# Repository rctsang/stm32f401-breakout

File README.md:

# STM32F401-Breakout

This is a breakout board for the STM32F401 using the [STM32F4Stamp](https://eleccelerator.com/stm32f4stamp-breakout-board/) (designed by Frank Zhao) as a reference.

It is untested, as this was only a personal project for gaining experience with PCB design.

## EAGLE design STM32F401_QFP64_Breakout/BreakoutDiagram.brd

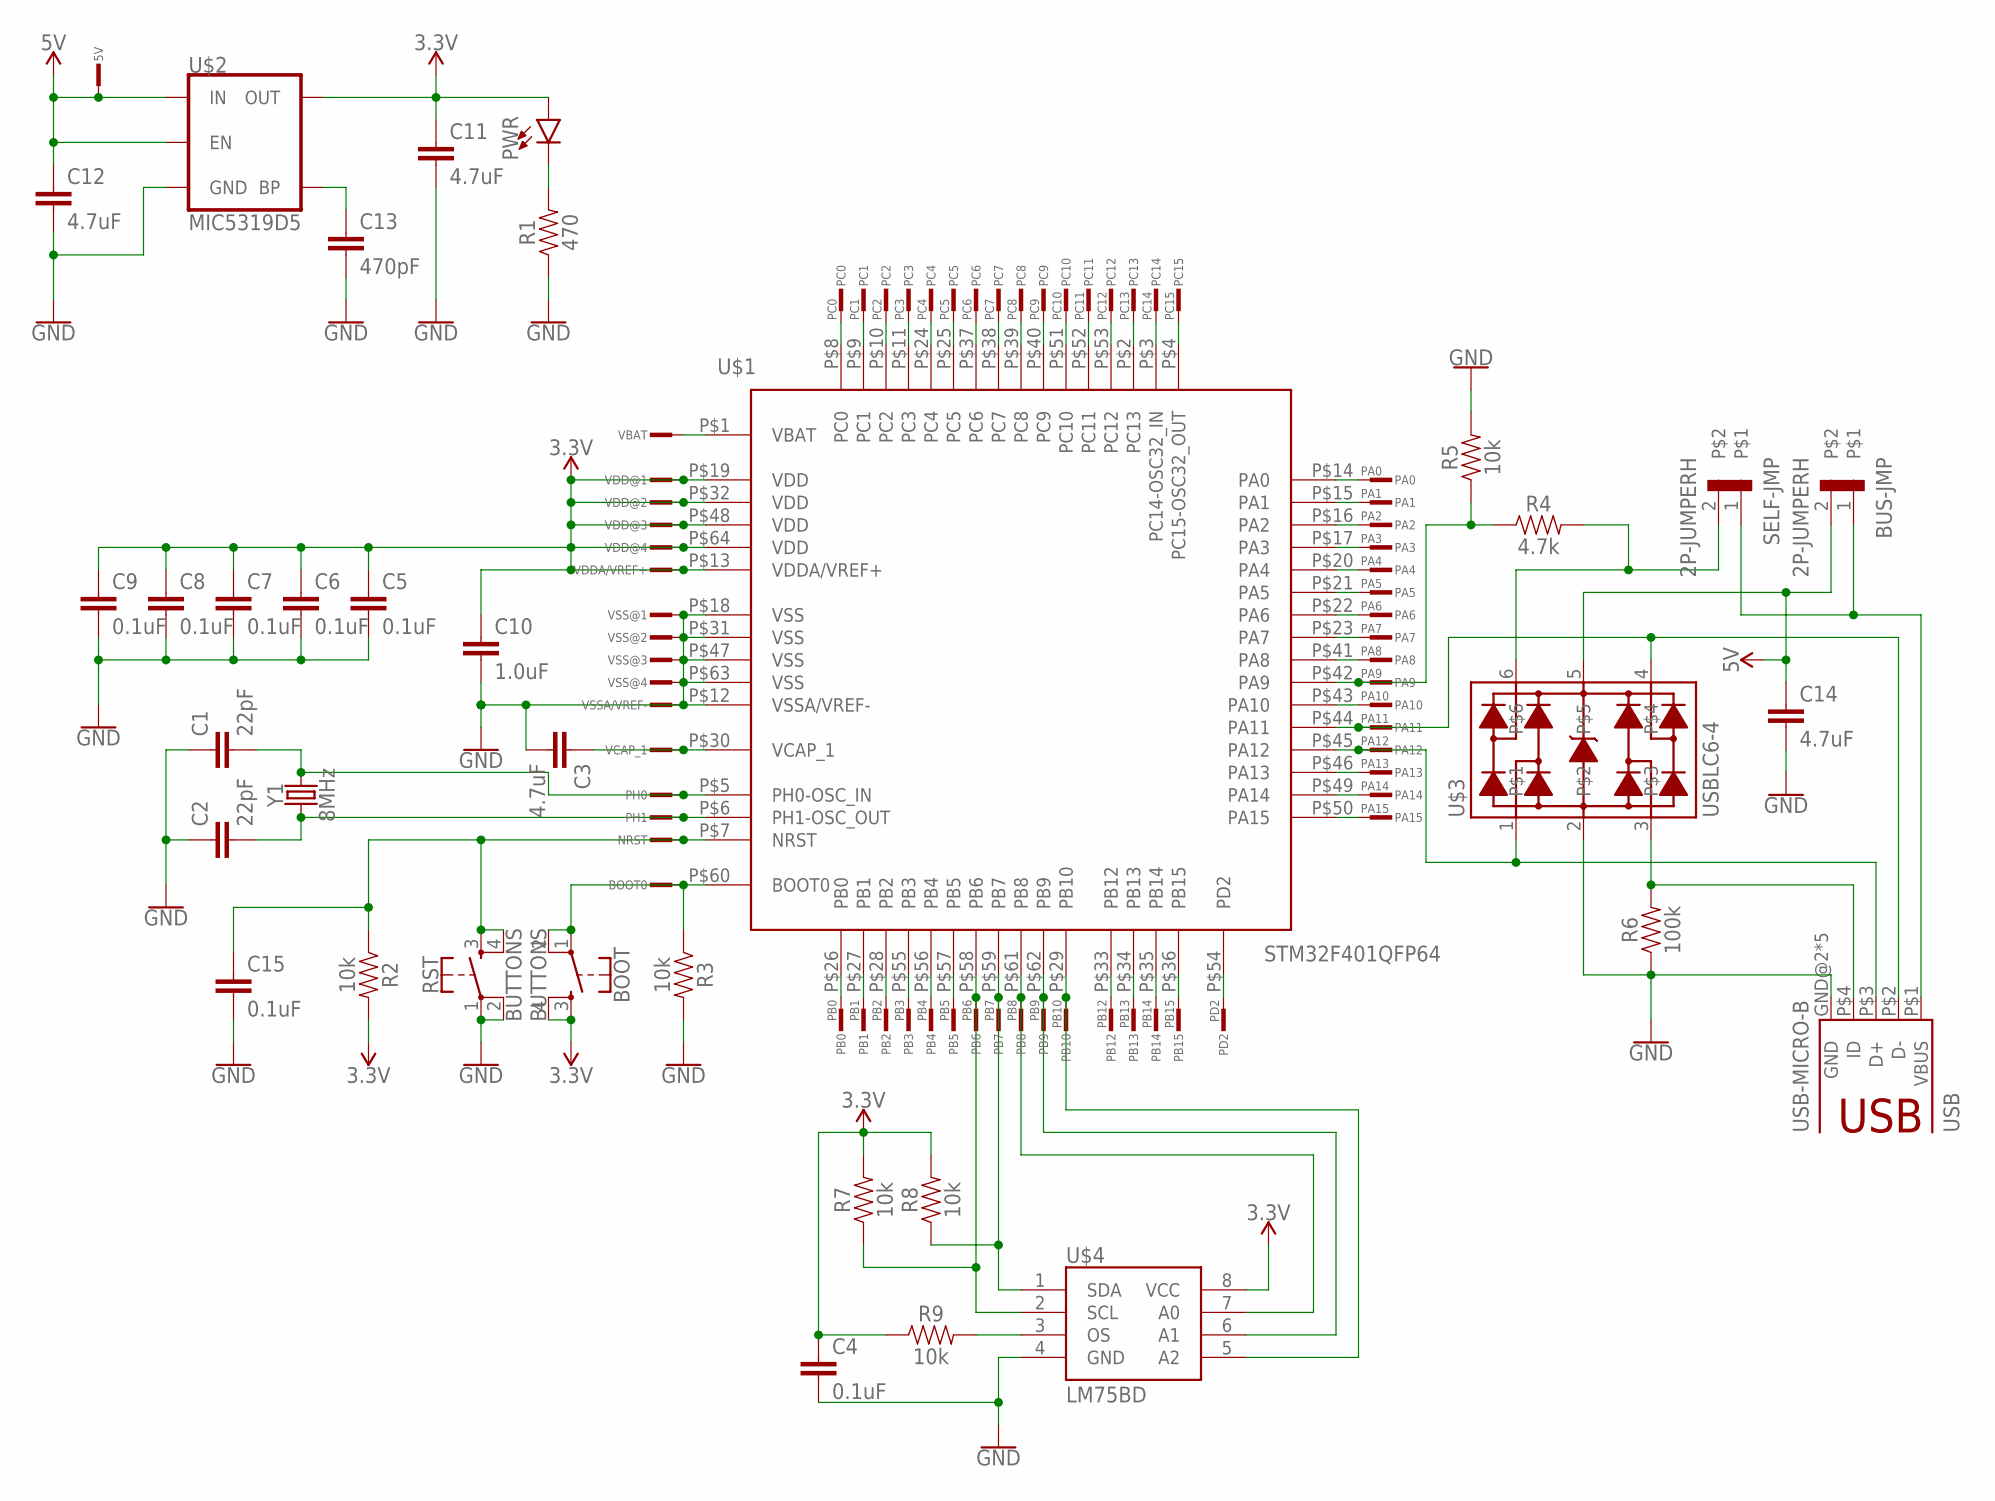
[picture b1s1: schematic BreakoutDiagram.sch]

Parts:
5V: PINV; 1X01
BOOT: BUTTONS; TACTILE_SWITCH_PTH_6.0MM
BOOT0: PINH; 1X01_HLABEL
BUS-JMP: 2P-JUMPERH; 1X02
C1, C2: 22pF; 0603
C3, C11, C12, C14: 4.7uF; 0603
C4, C15: 0.1uF; 0603
C5, C6, C7, C8, C9: 0.1uF; 0402
C10: 1.0uF; 0603
C13: 470pF; 0603
NRST: PINH; 1X01_HLABEL
PA0, PA1, PA2, PA3, PA4, PA5, PA6, PA7, PA8, PA9, PA10, PA11, PA12, PA13, PA14, PA15: PINH; 1X01_HLABEL
PB0, PB1, PB2, PB3, PB4, PB5, PB6, PB7, PB8, PB9, PB10, PB12, PB13, PB14, PB15: PINH; 1X01_HLABEL
PC0, PC1, PC2, PC3, PC4, PC5, PC6, PC7, PC8, PC9, PC10, PC11, PC12, PC13, PC14, PC15: PINH; 1X01_HLABEL
PD2: PINH; 1X01_HLABEL
PH0, PH1: PINH; 1X01_HLABEL
PWR: LED0603; LED-0603
R1: 470; 0402
R2, R3, R7, R8, R9: 10k; 0402
R4: 4.7k; 0603
R5: 10k; 0603
R6: 100k; 0603
RST: BUTTONS; TACTILE_SWITCH_PTH_6.0MM
SELF-JMP: 2P-JUMPERH; 1X02
U$1: STM32F401QFP64; LQFP64
U$2: MIC5319D5; SOT23-5
U$3: USBLC6-4; SOT23-6L
U$4: LM75BD; SO8
USB: USB-MICRO-B; USB-MICRO-B_SMD_CUT
VBAT: PINH; 1X01_HLABEL
VCAP_1: PINH; 1X01_HLABEL
VDD@1, VDD@2, VDD@3, VDD@4: PINH; 1X01_HLABEL
VDDA/VREF+: PINH; 1X01_HLABEL
VSS@1, VSS@2, VSS@3, VSS@4: PINH; 1X01_HLABEL
VSSA/VREF-: PINH; 1X01_HLABEL
Y1: 8MHz; CRYSTAL-SMD-5X3.2-2PAD

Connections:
3.3V: BOOT.3, BOOT.4, C4.1, C5.1, C6.1, C7.1, C8.1, C9.1, C10.1, C11.1, PWR.A, R2.2, R7.2, R8.2, R9.1, U$1.P$13 (VDDA/VREF+), U$1.P$19 (VDD), U$1.P$32 (VDD), U$1.P$48 (VDD), U$1.P$64 (VDD), U$2.5 (OUT), U$4.8 (VCC), VDD@1.1, VDD@2.1, VDD@3.1, VDD@4.1, VDDA/VREF+.1
5V: 5V.1, BUS-JMP.2, C12.1, C14.1, U$2.1 (IN), U$2.3 (EN), U$3.5
GND: C1.1, C2.1, C3.2, C4.2, C5.2, C6.2, C7.2, C8.2, C9.2, C10.2, C11.2, C12.2, C13.2, C14.2, C15.2, R1.1, R3.2, R5.2, R6.1, RST.1, RST.2, U$1.P$12 (VSSA/VREF-), U$1.P$18 (VSS), U$1.P$31 (VSS), U$1.P$47 (VSS), U$1.P$63 (VSS), U$2.2 (GND), U$3.2, U$4.4 (GND), USB.GND@2 (GND), USB.GND@3 (GND), USB.GND@4 (GND), USB.GND@5 (GND), USB.P$5 (GND), VSS@1.1, VSS@2.1, VSS@3.1, VSS@4.1, VSSA/VREF-.1
unnamed: C2.2, PH1.1, U$1.P$6 (PH1-OSC_OUT), Y1.P$1 (1)
unnamed: C1.2, PH0.1, U$1.P$5 (PH0-OSC_IN), Y1.P$2 (2)
unnamed: C3.1, U$1.P$30 (VCAP_1), VCAP_1.1
unnamed: PWR.C, R1.2
unnamed: C13.1, U$2.4 (BP)
unnamed: C15.1, NRST.1, R2.1, RST.3, RST.4, U$1.P$7 (NRST)
unnamed: BOOT.1, BOOT.2, BOOT0.1, R3.1, U$1.P$60 (BOOT0)
unnamed: R9.2, U$4.3 (OS)
unnamed: BUS-JMP.1, SELF-JMP.1, USB.P$1 (VBUS)
unnamed: R4.2, SELF-JMP.2, U$3.6
unnamed: R6.2, U$3.3, USB.P$4 (ID)
unnamed: U$1.P$1 (VBAT), VBAT.1
PA0: PA0.1, U$1.P$14 (PA0)
PA1: PA1.1, U$1.P$15 (PA1)
PA2: PA2.1, U$1.P$16 (PA2)
PA3: PA3.1, U$1.P$17 (PA3)
PA4: PA4.1, U$1.P$20 (PA4)
PA5: PA5.1, U$1.P$21 (PA5)
PA6: PA6.1, U$1.P$22 (PA6)
PA7: PA7.1, U$1.P$23 (PA7)
PA8: PA8.1, U$1.P$41 (PA8)
PA9: PA9.1, R4.1, R5.1, U$1.P$42 (PA9)
PA10: PA10.1, U$1.P$43 (PA10)
PA11: PA11.1, U$1.P$44 (PA11), U$3.4, USB.P$2 (D-)
PA12: PA12.1, U$1.P$45 (PA12), U$3.1, USB.P$3 (D+)
PA13: PA13.1, U$1.P$46 (PA13)
PA14: PA14.1, U$1.P$49 (PA14)
PA15: PA15.1, U$1.P$50 (PA15)
PB0: PB0.1, U$1.P$26 (PB0)
PB1: PB1.1, U$1.P$27 (PB1)
PB2: PB2.1, U$1.P$28 (PB2)
PB3: PB3.1, U$1.P$55 (PB3)
PB4: PB4.1, U$1.P$56 (PB4)
PB5: PB5.1, U$1.P$57 (PB5)
PB6: PB6.1, R7.1, U$1.P$58 (PB6), U$4.2 (SCL)
PB7: PB7.1, R8.1, U$1.P$59 (PB7), U$4.1 (SDA)
PB8: PB8.1, U$1.P$61 (PB8), U$4.7 (A0)
PB9: PB9.1, U$1.P$62 (PB9), U$4.6 (A1)
PB10: PB10.1, U$1.P$29 (PB10), U$4.5 (A2)
PB12: PB12.1, U$1.P$33 (PB12)
PB13: PB13.1, U$1.P$34 (PB13)
PB14: PB14.1, U$1.P$35 (PB14)
PB15: PB15.1, U$1.P$36 (PB15)
PC0: PC0.1, U$1.P$8 (PC0)
PC1: PC1.1, U$1.P$9 (PC1)
PC2: PC2.1, U$1.P$10 (PC2)
PC3: PC3.1, U$1.P$11 (PC3)
PC4: PC4.1, U$1.P$24 (PC4)
PC5: PC5.1, U$1.P$25 (PC5)
PC6: PC6.1, U$1.P$37 (PC6)
PC7: PC7.1, U$1.P$38 (PC7)
PC8: PC8.1, U$1.P$39 (PC8)
PC9: PC9.1, U$1.P$40 (PC9)
PC10: PC10.1, U$1.P$51 (PC10)
PC11: PC11.1, U$1.P$52 (PC11)
PC12: PC12.1, U$1.P$53 (PC12)
PC13: PC13.1, U$1.P$2 (PC13)
PC14: PC14.1, U$1.P$3 (PC14-OSC32_IN)
PC15: PC15.1, U$1.P$4 (PC15-OSC32_OUT)
PD2: PD2.1, U$1.P$54 (PD2)

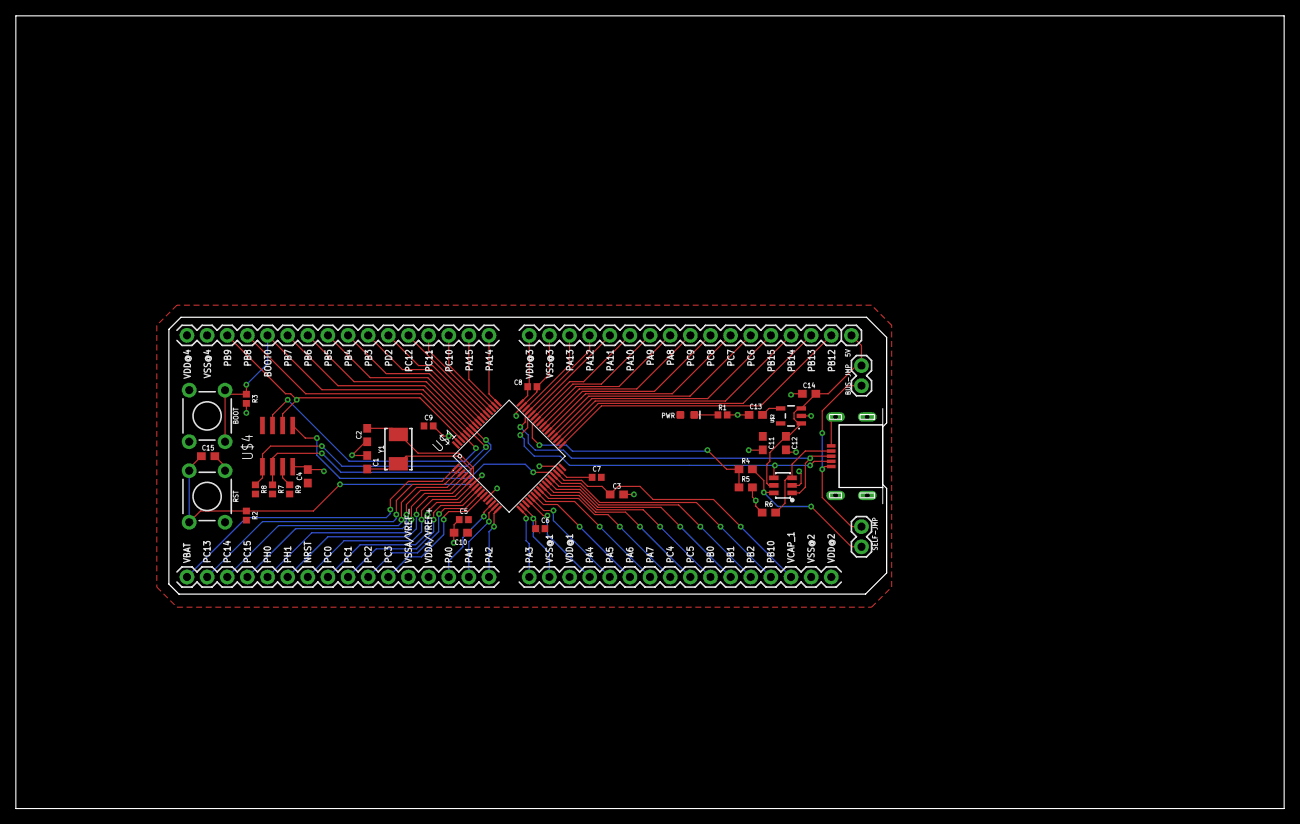
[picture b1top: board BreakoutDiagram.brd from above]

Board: 2 copper layers, 159.8 x 99.8 mm, 100 parts (0 on the bottom side), 63 nets.

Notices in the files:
parts and their libraries:
SparkFun-Capacitors: Licensing: Creative Commons ShareAlike 4.0 International - https://creativecommons.org/licenses/by-sa/4.0
